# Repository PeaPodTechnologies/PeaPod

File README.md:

# PeaPod <!-- omit in toc -->

A cloud-connected isolated and automated plant growth environment, able to generate any environment from a combination of independent environment parameters. 

Designed as both a hassle-free food production system and a research tool for precise and distributed mapping of the plant-environment relationship.

<!-- TODO: Build statuses? etc. -->

Submitted to the [NASA/CSA Deep Space Food Challenge](https://impact.canada.ca/en/challenges/deep-space-food-challenge). _Update_: PeaPod has [won](https://impact.canada.ca/en/challenges/deep-space-food-challenge/semi-finalists) Phase 1 and moved on to prototyping for Phase 2!

***

### Table of Contents

- [Background](#background)
  - [Features](#features)
- [Production](#production)
- [Development](#development)
- [Contribution](#contribution)
  - [New Issue](#new-issue)
  - [Existing Issues](#existing-issues)
- [Acknowledgements](#acknowledgements)

<!-- include some visuals, i.e. a 3D GIF of the CAD, maybe a flowchart/diagram -->

***

## Background

See our [requirements document](https://github.com/PeaPodTechnologies/PeaPod/blob/staging/docs/requirements/Requirements.pdf).

### Features

See our [progress report](https://github.com/PeaPodTechnologies/PeaPod/blob/staging/docs/RrogressReport.pdf).

<!-- ### Innovations
PeaPod is *not* a fancy container with a light stand. 

PeaPod can **precisely** replicate climates for optimal growing conditions, and also has the ability to collect plant growth data during the growing cycle. 
This data is then used to further *optimize climate parameters* so food grown in PeaPods will taste better over time.

PeaPod is *modular* and *easy to assemble*. 
Construction with aluminum extrusion allows PeaPods to be transported like IKEA furniture, useful for situations where a lot of food is required at the end of a long journey. 
A lot of PeaPods can be collapsed into a tiny space. 
This also means PeaPods can be configured to be any size to grow any type of plant.

PeaPod is self-optimizing, versatile, easy to assemble, and it makes food. -->

***

## Production

<!-- ### Assembly

### Installation

w/ examples, i.e. GIF of expected output, inline code -->

TBA.

***

## Development
<!-- dependencies, environment, languages -->

> See [`software/README`](software/README.md#Development) and the individual [`subsystems`](/subsystems/README.md) for development details.

<br>

## Contribution

### New Issue

1. Open an issue with the features you'd like to add/bugs you'd like to see squashed (admins will add labels, assignments, etc.)
2. Discuss the scope and specifics in the issue, and either:
   1. Make a new branch, make changes, open a **PR Draft** (if you have permissions); or
   2. Fork this repo, make changes, open a **PR Draft**.
3. Request review by changing the **PR Draft** to a full-blown **PR** when you think it's ready.
4. If the reviewer(s) accept the changes, they will merge the **PR** and close the related issue.

### Existing Issues

Check out our [open issues](https://github.com/PeaPodTechnologies/PeaPod/issues?q=is%3Aopen+is%3Aissue+label%3A%22Status%3A+Open%22)!

<!-- ### Support -->
<!-- issues page, discussion board/Discord? -->

<br>

## Acknowledgements

Sincere thanks to the following individuals and groups:
- MIT Media Lab's Open Agriculture Initiative (for inspiration)
- The Open Source community
- Deep Space Food Challenge administrators and participants

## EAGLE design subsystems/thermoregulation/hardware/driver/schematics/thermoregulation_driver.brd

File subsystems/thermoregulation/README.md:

# PeaPod Thermoregulation Subsystem

## Purchasing

TODO: Notes on PCB ordering, multiple BoMs, etc.

## Assembly

## Testing

### Method

### Results

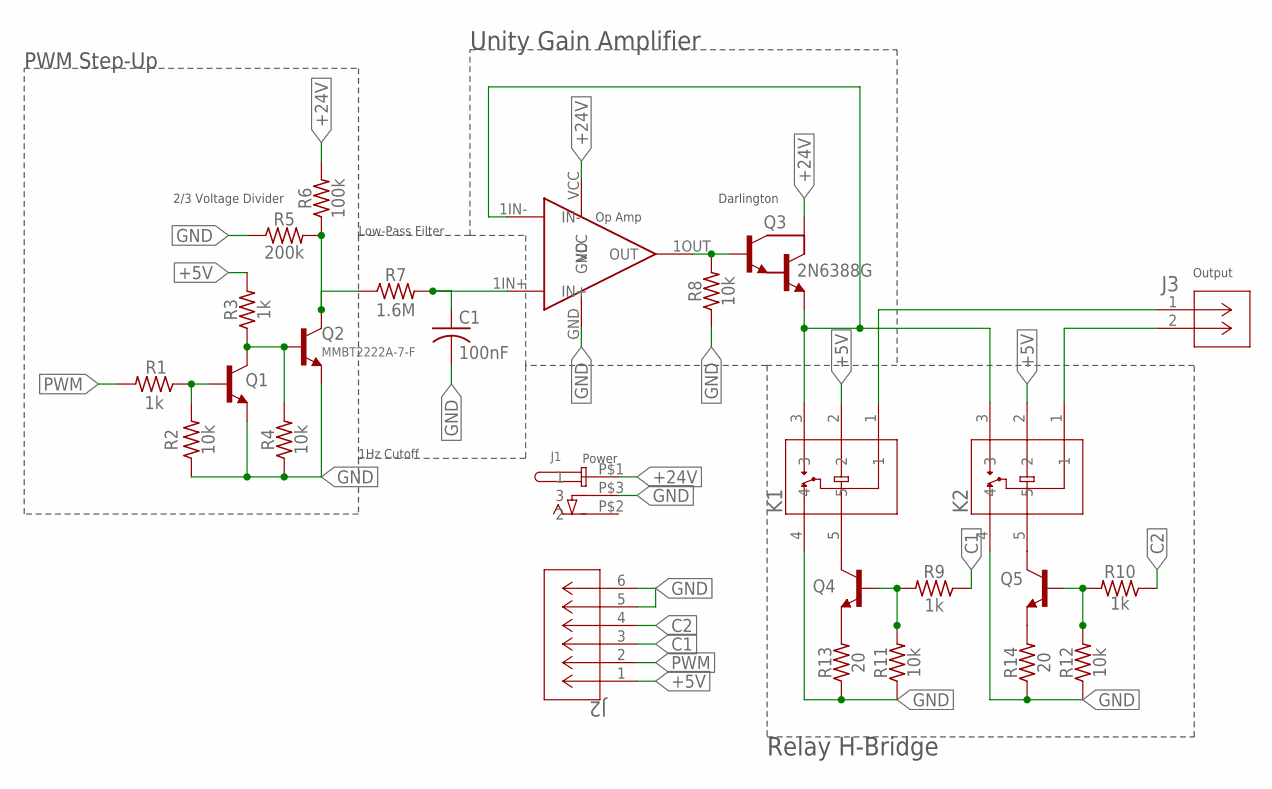
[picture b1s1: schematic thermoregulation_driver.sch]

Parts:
C1: 100nF; CAPC1005X60
J1: DCBARRELJACK
J2: MOLEX-MICROLOCK-6PIN; CON_5055670671
J3: 436500201CON_436500201_MOL; CON_436500201_MOL
K1, K2: G5LE-14_DC12RELAY_G5LE-1_DC5_OMR; RELAY_G5LE-1_DC5_OMR
OPAMP1: LM324N
Q1, Q4, Q5: NPN; SOT95P237X112-3N
Q2: MMBT2222A-7-F; SOT95P237X112-3N
Q3: 2N6388G; TO220
R1, R3, R9, R10: 1k; RESC1005X40
R2, R4, R8, R11, R12: 10k; RESC1005X40
R5: 200k; RESC1005X40
R6: 100k; RESC1005X40
R7: 1.6M; RESC1005X40
R13, R14: 20; RESC2012X65

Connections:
+5V: J2.1, K1.2, K2.2, R3.2
+24V: J1.P$1 (1), OPAMP1.VCC, Q3.C, R6.2
C1: J2.3, R9.1
C2: J2.4, R10.1
GND: C1.2, J1.P$3 (3), J2.5, J2.6, K1.4, K2.4, OPAMP1.GND, Q1.2 (E), Q2.2 (E), R2.1, R4.1, R5.1, R8.1, R11.1, R12.1, R13.1, R14.1
unnamed: Q2.3 (C), R5.2, R6.1, R7.1
unnamed: Q1.3 (C), Q2.1 (B), R3.1, R4.2
unnamed: C1.1, OPAMP1.1IN+ (IN+), R7.2
unnamed: OPAMP1.1OUT (OUT), Q3.B, R8.2
unnamed: Q1.1 (B), R1.1, R2.2
unnamed: K1.3, K2.3, OPAMP1.1IN- (IN-), Q3.E
unnamed: J3.1, K1.1
unnamed: J3.2, K2.1
unnamed: K1.5, Q4.3 (C)
unnamed: K2.5, Q5.3 (C)
unnamed: Q4.1 (B), R9.2, R11.2
unnamed: Q5.1 (B), R10.2, R12.2
unnamed: Q4.2 (E), R13.2
unnamed: Q5.2 (E), R14.2
PWM: J2.2, R1.2

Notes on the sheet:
PWM Step-Up
Low-Pass Filter
1Hz Cutoff
2/3 Voltage Divider
Unity Gain Amplifier
Darlington
Op Amp
Relay H-Bridge
Output
Power

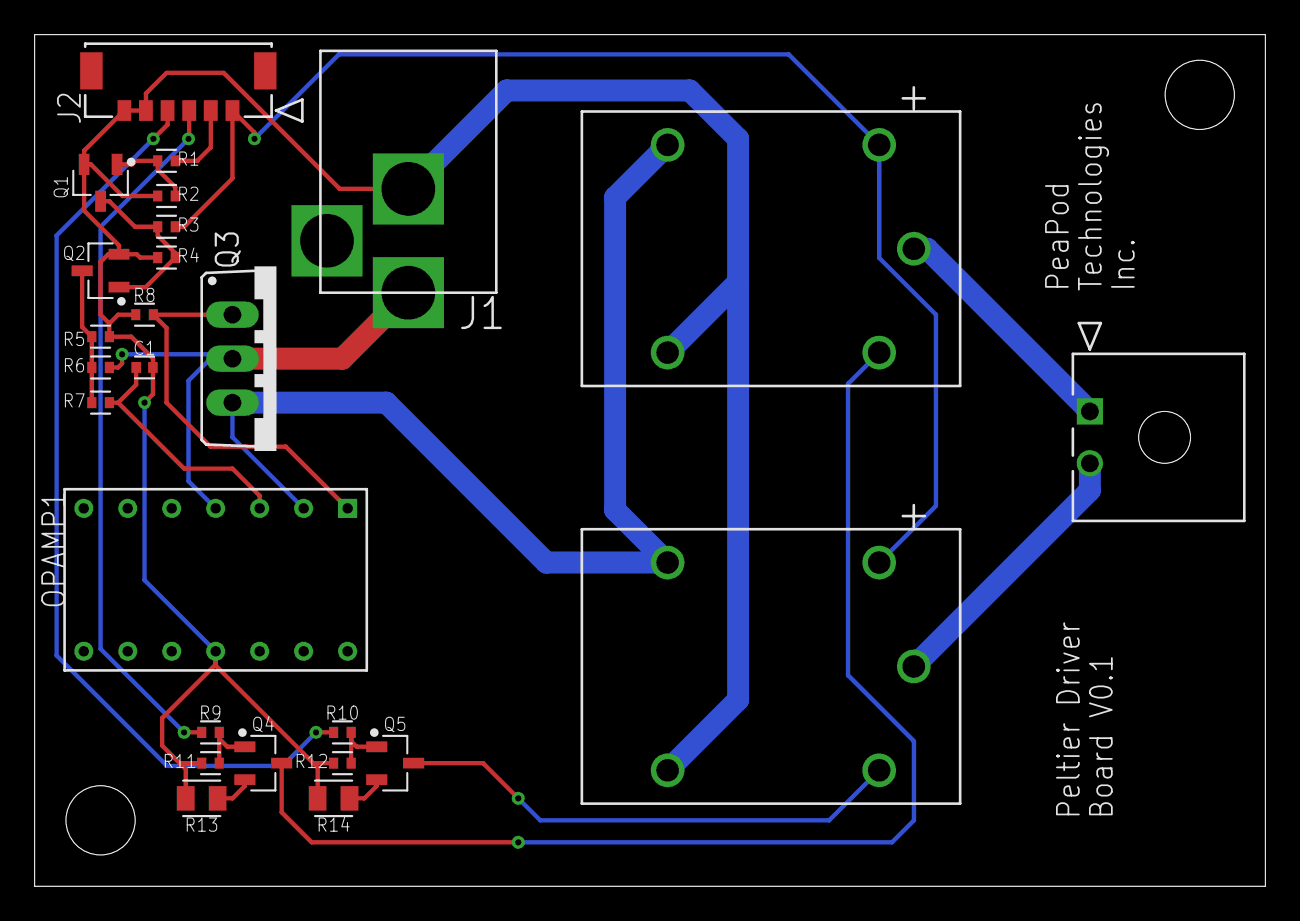
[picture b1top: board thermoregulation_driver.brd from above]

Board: 2 copper layers, 71.1 x 49.2 mm, 26 parts (0 on the bottom side), 20 nets.

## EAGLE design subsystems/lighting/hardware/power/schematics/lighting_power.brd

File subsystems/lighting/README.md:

# PeaPod Lighting Subsystem

See `./REQUIREMENTS.md` for the subsystem requirements.

Provides controlled light to the plant canopy and supports programmable photoperiods (on/off), light intensity (dimming), and spectral channel control via Adafruit PCA9685 PWM dimming of MEAN WELL LDD-L constant-current LED drivers powering CREE XLAMP LEDs with a variety of spectra, including PAR and white for imaging. Power regulator, I2C cables, and PCBs are documented swappable components.

# Production

## Assembly

### Bills of Materials

<!-- TODO: Cables?? -->

See `./hardware/lighting_bom_purchase.csv` for the purchase bill of materials. See `./hardware/gerber/` for PCB manufacturing files (NOTE: STENCIL NECESSARY). See `./hardware/lighting_bom_components.csv` for the electronic components bill of materials (DigiKey).

1. 1 x Lighting BOM Components per led board
2. 1 x Lighting BOM Purchase per led board

### Tools and Equipment

Required:
- Soldering Iron, Solder, and Flux
- Wire Strippers (20-30 AWG)
- Reflow Oven (or hot air rework station) and solder paste
- Putty Scraper

Optional, but recommended:
- Helping Hands (for soldering)
- Multimeter (for testing connections)
- Oscilloscope (for testing signal integrity)
- Luminous Flux Meter (for measuring light output)

## Instructions

1. Using a putty scraper, apply solder paste to the PCB using the stencil.
2. Place the surface-mount components (signal connector, resistor, and LEDs) on the PCB according to the silkscreen.
3. Reflow the PCB in a reflow oven (or use a hot air rework station) to solder the surface-mount components.
4. Solder the through-hole components (power connector and LED driver) to the PCB according to the silkscreen.

## Testing

### Power Test

**Protocol**: Connect the 24V power supply (+24VDC and GND) to the power connector on the PCB.

**Validation**: Nothing happens. Test points TP3 and TP4 read +24V and 0V, respectively.

**Failure Protocol**: 

1. *Smoke, Sparks or Unusual Heat/Odors*: Immediately disconnect the power supply. Check the PCB for solder bridges or shorts. If issue persists, check the power supply and ensure it is functioning correctly.

2. *Incorrect Voltage Readings*: Check the power supply connections and ensure the PCB is properly soldered.

### LED Light Test

**Protocol**: Connect the 24V power supply (+24VDC and GND) to the power connector on the PCB. Flash an Arduino-compatible microcontroller with the `./software/tests/Test_SingleWave/Test_SingleWave.ino` sketch. Connect the microcontroller to the signal connector on the PCB (Digital Pin 3 and GND). Observe the behavior of the LEDs.

**Validation**: The LEDs should light up in a sinusoidal wave pattern, with the brightness varying smoothly over time.

**Failure Protocol**: Check the power supply connections and ensure the PCB is properly soldered. Check test points TP3 and TP4 for correct voltage levels. Check the microcontroller connections to the signal connector and ensure the correct pin is used. Check test point TP5 for PWM signal using an oscilloscope. If issue persists, check the microcontroller code and ensure it is functioning correctly.

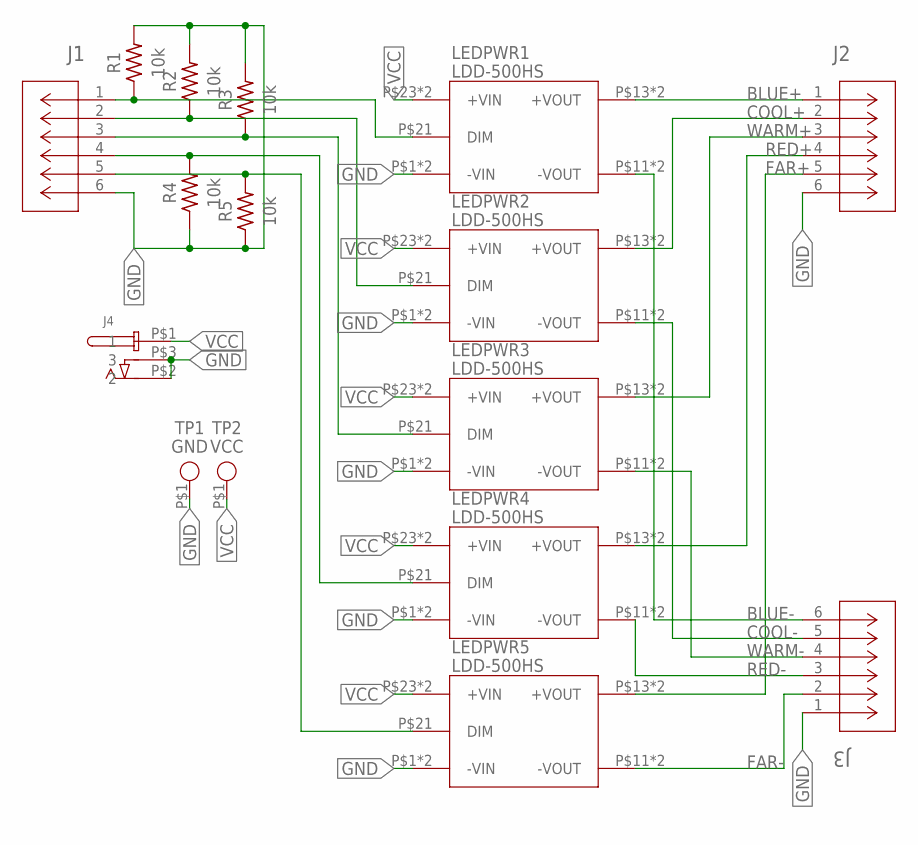
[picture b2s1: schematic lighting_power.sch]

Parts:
J1, J2, J3: MOLEX-MICROLOCK-6PIN; CON_5055670671
J4: DCBARRELJACK
LEDPWR1, LEDPWR2, LEDPWR3, LEDPWR4, LEDPWR5: LDD-500HS; LDD-300~1000HS
R1, R2, R3, R4, R5: 10k; RESC1005X40
TP1: GND; TP_CIRCLE_2.5MM
TP2: VCC; TP_CIRCLE_2.5MM

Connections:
BLUE+: J2.1, LEDPWR1.P$13 (+VOUT), LEDPWR1.P$14 (+VOUT)
BLUE-: J3.6, LEDPWR1.P$11 (-VOUT), LEDPWR1.P$12 (-VOUT)
COOL+: J2.2, LEDPWR2.P$13 (+VOUT), LEDPWR2.P$14 (+VOUT)
COOL-: J3.5, LEDPWR2.P$11 (-VOUT), LEDPWR2.P$12 (-VOUT)
FAR+: J2.5, LEDPWR5.P$13 (+VOUT), LEDPWR5.P$14 (+VOUT)
FAR-: J3.2, LEDPWR5.P$11 (-VOUT), LEDPWR5.P$12 (-VOUT)
GND: J1.6, J2.6, J3.1, J4.P$3 (3), LEDPWR1.P$1 (-VIN), LEDPWR1.P$2 (-VIN), LEDPWR2.P$1 (-VIN), LEDPWR2.P$2 (-VIN), LEDPWR3.P$1 (-VIN), LEDPWR3.P$2 (-VIN), LEDPWR4.P$1 (-VIN), LEDPWR4.P$2 (-VIN), LEDPWR5.P$1 (-VIN), LEDPWR5.P$2 (-VIN), R1.2, R2.2, R3.2, R4.1, R5.1, TP1.P$1
unnamed: J1.1, LEDPWR1.P$21 (DIM), R1.1
unnamed: J1.2, LEDPWR2.P$21 (DIM), R2.1
unnamed: J1.3, LEDPWR3.P$21 (DIM), R3.1
unnamed: J1.4, LEDPWR4.P$21 (DIM), R4.2
unnamed: J1.5, LEDPWR5.P$21 (DIM), R5.2
RED+: J2.4, LEDPWR4.P$13 (+VOUT), LEDPWR4.P$14 (+VOUT)
RED-: J3.3, LEDPWR4.P$11 (-VOUT), LEDPWR4.P$12 (-VOUT)
VCC: J4.P$1 (1), LEDPWR1.P$23 (+VIN), LEDPWR1.P$24 (+VIN), LEDPWR2.P$23 (+VIN), LEDPWR2.P$24 (+VIN), LEDPWR3.P$23 (+VIN), LEDPWR3.P$24 (+VIN), LEDPWR4.P$23 (+VIN), LEDPWR4.P$24 (+VIN), LEDPWR5.P$23 (+VIN), LEDPWR5.P$24 (+VIN), TP2.P$1
WARM+: J2.3, LEDPWR3.P$13 (+VOUT), LEDPWR3.P$14 (+VOUT)
WARM-: J3.4, LEDPWR3.P$11 (-VOUT), LEDPWR3.P$12 (-VOUT)

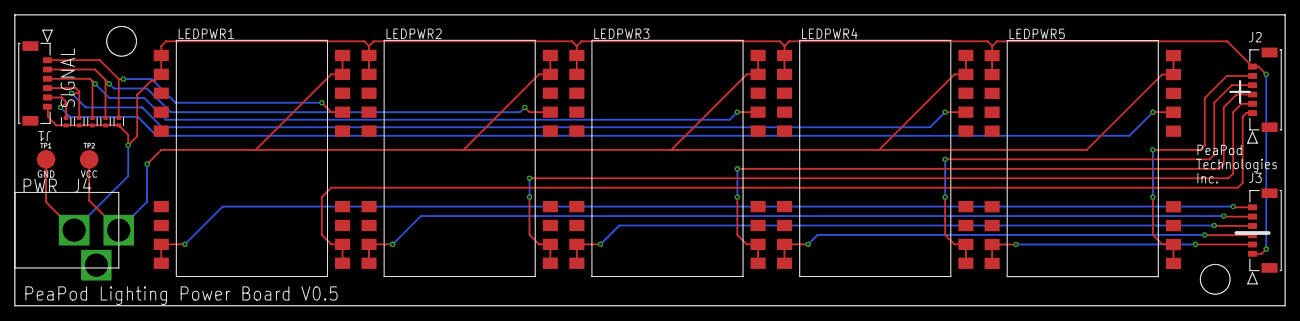
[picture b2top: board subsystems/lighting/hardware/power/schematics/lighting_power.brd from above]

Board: 2 copper layers, 170.8 x 39.1 mm, 16 parts (0 on the bottom side), 17 nets.

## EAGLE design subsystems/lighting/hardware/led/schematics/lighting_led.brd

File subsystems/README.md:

# PeaPod Subsystems

All subsystems will follow the same structure:

- `README.md` - Detailed instructions for fabrication and purchasing, list of materials incl. tools, assembly instructions with graphics, testing and validation protocol, method of operation, and expected results.
- `REQUIREMENTS.md`
- `assets/` - various graphical/etc. assets (diagrams, etc. excluding pictures of schematics/PCB layouts)
- `hardware/`
- `software/`

In addition, each subsystem should have its own `README.MD` with the following info:

- Purchasing
- Assembly w/ photos
- Testing (process and results)

## Hardware

Includes all **reference** bills of materials (BOM), 3D printing files, PCB files, etc.

Subdirectories:

- `boms/` - Bills of Materials (CSV files)
- `fabrication/` - Fabricated part files (i.e. 3D printing files)
- `schematics/` - PCB schematics (.SCH and .BRD files and photos of each)
- `gerber/` - Gerber files (PCB manufacturing)

## Software

Includes all C/C++ libraries and Arduino testing scripts.

Subdirectories:

- `src/` - Libraries
- `tests/` - Test scripts

# Development

Component BOMs downloaded from [DigiKey](https://www.digikey.ca) (can be directly uploaded for ordering). All other BoM types (fabrication, purchase, etc.) copied from the [BoM Templates](/.github/BOM_TEMPLATES/). 3D models, PCB and schematic docs are made using [AutoDesk Fusion 360](https://www.autodesk.ca/en/products/fusion-360/overview).

## Requirements

- Fusion 360 or your 3D editor of choice
- EasyEDA or your PCB/schematic editor(s) of choice
- Excel/Google Sheets or your CSV reader/spreadsheet software of choice

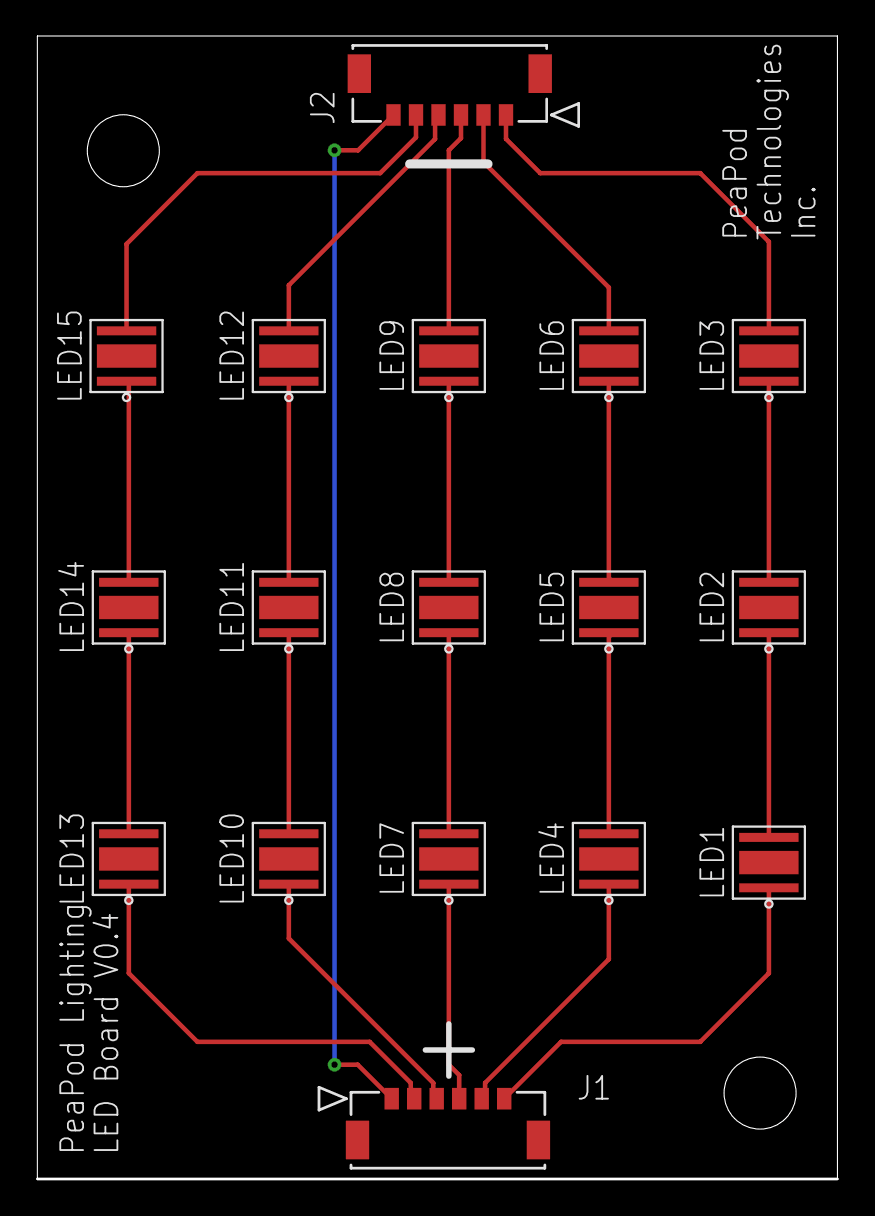
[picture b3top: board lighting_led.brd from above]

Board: 2 copper layers, 44.5 x 63.4 mm, 17 parts (0 on the bottom side), 21 nets.

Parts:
J1, J2: MOLEX-MICROLOCK-6PIN; CON_5055670671
LED1, LED2, LED3: XP-G3_BLUE; XLAMP_XP-G3_BLUE
LED4, LED5, LED6: XP-G3_COOL; XLAMP_XP-G3_COOL
LED7, LED8, LED9: XP-G3_WARM; XLAMP_XP-G3_WARM
LED10, LED11, LED12: XP-G3_RED; XLAMP_XP-G3_RED
LED13, LED14, LED15: XLAMP_XP-E2

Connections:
unnamed: LED4.P$2, LED5.P$1
unnamed: LED1.P$2, LED2.P$1
unnamed: LED2.P$2, LED3.P$1
unnamed: LED5.P$2, LED6.P$1
unnamed: LED7.P$2, LED8.P$1
unnamed: LED8.P$2, LED9.P$1
unnamed: LED10.P$2, LED11.P$1
unnamed: LED11.P$2, LED12.P$1
unnamed: LED13.P$2, LED14.P$1
unnamed: LED14.P$2, LED15.P$1
unnamed: J1.6, LED1.P$1
unnamed: J1.5, LED4.P$1
unnamed: J1.4, LED7.P$1
unnamed: J1.3, LED10.P$1
unnamed: J1.2, LED13.P$1
unnamed: J1.1, J2.6
unnamed: J2.5, LED15.P$2
unnamed: J2.4, LED12.P$2
unnamed: J2.3, LED9.P$2
unnamed: J2.2, LED6.P$2
unnamed: J2.1, LED3.P$2

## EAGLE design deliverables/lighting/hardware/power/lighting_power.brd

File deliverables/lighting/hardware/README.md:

# Lighting Hardware

TODO: Notes on PCB ordering, multiple BoMs, etc.

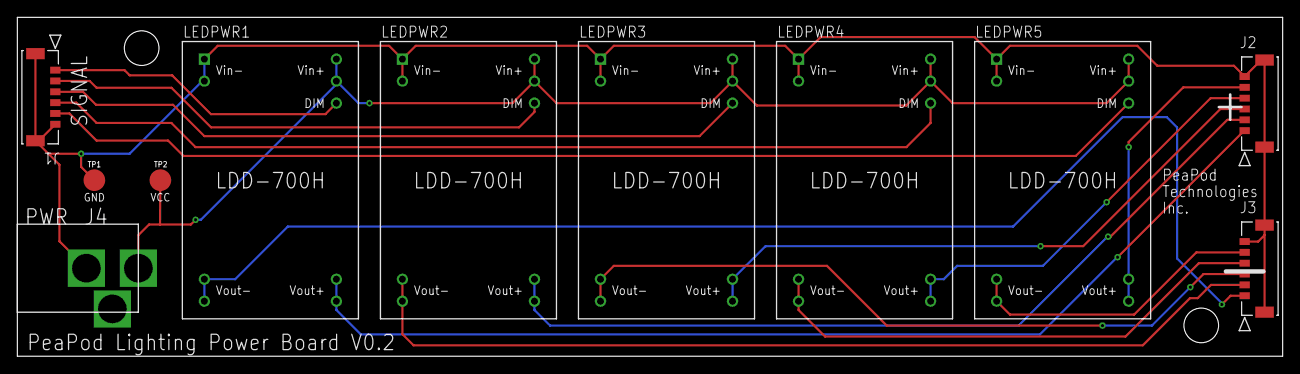
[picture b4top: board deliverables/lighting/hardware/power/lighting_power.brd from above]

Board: 2 copper layers, 146.1 x 39.1 mm, 11 parts (0 on the bottom side), 17 nets.

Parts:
J1, J2, J3: MOLEX-MICROLOCK-6PIN; CON_5055670671
J4: DCBARRELJACK
LEDPWR1, LEDPWR2, LEDPWR3, LEDPWR4, LEDPWR5: LDD-700H; NLDD-300~1000H
TP1: GND; TP_CIRCLE_2.5MM
TP2: VCC; TP_CIRCLE_2.5MM

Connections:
GND: J1.6, J1.7, J1.8, J2.6, J2.7, J2.8, J3.6, J3.7, J3.8, J4.P$3, LEDPWR1.VIN-1, LEDPWR1.VIN-2, LEDPWR2.VIN-1, LEDPWR2.VIN-2, LEDPWR3.VIN-1, LEDPWR3.VIN-2, LEDPWR4.VIN-1, LEDPWR4.VIN-2, LEDPWR5.VIN-1, LEDPWR5.VIN-2, TP1.P$1
unnamed: J1.1, LEDPWR1.DIM
unnamed: J1.2, LEDPWR2.DIM
unnamed: J1.3, LEDPWR3.DIM
unnamed: J1.4, LEDPWR4.DIM
unnamed: J1.5, LEDPWR5.DIM
unnamed: J2.1, LEDPWR1.VO+1, LEDPWR1.VO+2
unnamed: J2.2, LEDPWR2.VO+1, LEDPWR2.VO+2
unnamed: J2.3, LEDPWR3.VO+1, LEDPWR3.VO+2
unnamed: J2.4, LEDPWR4.VO+1, LEDPWR4.VO+2
unnamed: J2.5, LEDPWR5.VO+1, LEDPWR5.VO+2
unnamed: J3.1, LEDPWR1.VO-1, LEDPWR1.VO-2
unnamed: J3.2, LEDPWR2.VO-1, LEDPWR2.VO-2
unnamed: J3.3, LEDPWR3.VO-1, LEDPWR3.VO-2
unnamed: J3.4, LEDPWR4.VO-1, LEDPWR4.VO-2
unnamed: J3.5, LEDPWR5.VO-1, LEDPWR5.VO-2
VCC: J4.P$1, LEDPWR1.VIN+1, LEDPWR1.VIN+2, LEDPWR2.VIN+1, LEDPWR2.VIN+2, LEDPWR3.VIN+1, LEDPWR3.VIN+2, LEDPWR4.VIN+1, LEDPWR4.VIN+2, LEDPWR5.VIN+1, LEDPWR5.VIN+2, TP2.P$1

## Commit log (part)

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2021-07-16 added storyboard frame revisions
2021-07-17 Removed Review Frames
2021-07-17 Added Setup Frames, Pollination
2021-07-18 Wrote Blockchain
2021-07-18 Revision, Formatting
2021-07-19 New Method Structure to Template
2021-07-19 Housing Method Revision
    formatted features
2021-07-19 Contact Info Formatting
2021-07-20 Nutrients, pH Method Revision
2021-07-20 Script Condensing, Modifying
2021-07-20 Injection Manifold Method Revision
2021-07-20 Added to safety of produce section
2021-07-20 Air Temperature Method Revision
    changed spacing
2021-07-20 Dehumidification Method Revision
2021-07-20 Solution Temperature Method Revision
2021-07-20 Optimization, Formatting, Justification Integration
2021-07-21 Updated Version
2021-07-21 revised
2021-07-21 revised
    @JonasMarshall
2021-07-22 Fixed PR#87
2021-07-22 Acceptability of Process pt. 1
2021-07-23 Fix Table of Contents
2021-07-24 Voiceover
2021-07-24 Setup Process Timing Estimates
2021-07-26 mentioned a recycling pump
2021-07-26 Acceptability of Products
2021-07-27 Added "Runoff"
2021-07-27 Better Terrestrial Prompts
2021-07-27 Script to Description Part A
    added basc to jonas's description
2021-07-27 Whole-Design Breakdown
    commented out figures
    rotated design process 90deg
2021-07-28 Update Customer-facing Food Service
2021-07-28 Update Crowdsourced Research
2021-07-28 Un-OOPS
2021-07-28 Description A: Optimization
2021-07-28 Update De-centralized Production
2021-07-28 Added first 1000 characters of innovation section
2021-07-28 Update Innovation
2021-07-28 Minor Fix
2021-07-29 Revisions
2021-07-29 Minor Fix 2: Electric Boogaloo
2021-07-29 Description Revision
2021-07-29 Copyright Ownership Transferred
2021-07-29 Final Script
    removed old voiceover
2021-07-30 1st Cut to Design Abstract
2021-07-30 3rd Cut to Design Abstract
    Sub char limit
2021-07-30 Citations Part A
2021-07-30 1st Cut to Part A
    Also final cut to Abstract
2021-07-30 2nd Cut to Part A
    2029 Characters Over
2021-07-30 Cut Description B
2021-07-30 Cut Constraints
    moved estimates to appendix
    fixed citations
2021-07-30 2nd Cut to Innovation
    487 characters over
2021-07-30 Final Cut to Innovation
    42 characters under
2021-07-30 Final Cut to Terrestrial
    13 characters under
2021-07-30 Cut Down Performance Criteria
2021-07-30 Formatting
2021-07-30 Namedropped Pollination
2021-07-30 Minor Additions
2021-07-31 Link to Animation in Readme
2021-08-01 Easier Open-Source Contribution
2021-08-05 Solution Overview: Insulation
2021-08-06 Finished Calculations
2021-08-17 Updated for Door
2021-09-13 Squashed commit of the following:
    commit edd2e320934a10050e6a734e7f221cd0c52407a9
    Author: Jayden Lefebvre <jayden.lefebvre55@gmail.com>
    Date: Mon Sep 13 15:41:54 2021 -0400
    Delete actuator class
    commit 215b883cccbcfc56583e870d5dec005db6cc2654
    Merge: 85135fe 7164cfe
2021-09-27 Siphon Injector, BoM updates
2021-09-28 Refactored to UpRoute
2021-10-13 Removed DSFC, Assembly Docs
2021-10-13 Added Validation, Verification to Design Issue Template
2021-10-13 BoM Updates
    Finished https://github.com/UpRouteFoundation/PeaPod/issues/50#issuecomment-877507976
    Made sure older listings matched CAD and prototype
    Left the ones that were going to be outdated eventually
2021-10-13 Dehumidification
2021-10-24 The FINAL Doc/License Refactor
2021-10-25 Lighting Boards V0.2
2021-10-25 Minor Changes
    Used built-in constrain function
    Removed LED brightness factor coefficient (allows full power addressing)
2021-10-26 Added Supporting Files for V0.2
    SCH, BRD, and PNG for both
    Also FBX models
2021-10-27 Added Aeroponics Input Connectors
2021-10-28 Structure Overhaul
2021-10-28 Fix Broken Links
2021-11-06 Cleanup
2021-11-10 Software Restructure
2021-11-10 Batch Publishing
    Also: batch data logging, better startup scripts, restructured main
2021-11-10 Publish Logging - Use Reduce
2021-11-10 Project/Run Select, Offline Publishing
2021-11-12 Multiple Small Changes
    Added Info Spinner
    Changed main from async to return Promise, better error handling
2021-11-14 Change Contact Emails
2021-11-16 Removed Panel Mounts
2021-11-16 Updated BoM References
    Also removed seal strip stl
2021-11-20 Microcontroller Communications
    Start Publisher before Arduino (reversed promise nesting order)
    Fixed serial parser piping
    Better console logging
    Fixed Arduino JSON handling (manual \n instead of println, full revision message)
2021-11-20 Moved Arduino Code to /software
    also renamed to PeaPodOS-Arduino
2021-11-20 Minor Updates
2021-11-26 Lighting V0.4
    FINALLY fixed the connector flipping error (hint: pin 1 goes to pin 6 EVERY TIME)
    Flipped LED series order (blue on bottom)
    More "bus"-like routing on power PCB
    Updated version number text on PCBs
2021-11-26 Standardized Trace Width
    10mil on all traces (~8C rise at .7A)
2021-12-31 Small Changes
2022-01-07 Added Phase 2 Instructions to References
2022-01-09 Modularized Reference Designs
2022-01-09 Added UTAG To Namecard
2022-01-09 Requirements Graph
2022-01-09 Outlined Progress Report
2022-01-11 Outlined Final Report, Cleanup
    modularizing reused sections
    docs/ readme
2022-01-16 Fixes
2022-01-27 Improved Calculations
    added thermal resistance calculations
    added peltier driver circuit
2022-01-27 Bump follow-redirects from 1.14.5 to 1.14.7 in /software
    Bumps [follow-redirects](https://github.com/follow-redirects/follow-redirects) from 1.14.5 to 1.14.7.
    - [Release notes](https://github.com/follow-redirects/follow-redirects/releases)
    - [Commits](https://github.com/follow-redirects/follow-redirects/compare/v1.14.5...v1.14.7)
    ---
    updated-dependencies:
    - dependency-name: follow-redirects
2022-01-27 LED Class Improvements
    led color enum, parsing to String
2022-02-03 Setup
2022-02-04 Peltier Driver V0.1
2022-02-11 early draft testing plan + control points
    basically a frame, need to ask questions then can fill it out properly
2022-02-21 Testing Suite, ICSP Flashing
    Tests: GPIO miniUART serial port functionality (loopback test), compilation and upload test (blink), revision check test
    Arduino compile and flash utility function (utils)
    Readme overhaul
    Removed deprecated Arduino libraries (scale, nau7802, float)
2022-03-02 Moved Report TeX Class
2022-03-02 Modularized Solution Overview
2022-03-04 Minor Changes
    Arduino accepts empty instruction set
    Fixed spinner log ui util
    Better C++ styling (header order, file naming, #include protection naming)
2022-03-04 Package v0.0.9
2022-03-16 Migrated to PlatformIO
    * Migrated to PlatformIO for compilation
    * Separated JSON messaging, instruction parsing into utility files
    * Moved globals to header
    + PIO Testing Suite
    * Updated README
2022-03-18 TypeScript Unit Testing
    * Fixed PIO unit testing
    * JSON messenger returns instead of printing to serial during unit tests
    * main.cc ignored during unit tests
    * Moved lib/ to src/
    + Setup jest
    + Utils unit tests
2022-03-19 Fixed Unit Tests
    * Fixed TS compiling for RPi Node version (12.22.x)
    * No longer running test_instructions or test_messenger (awaiting fix)
2022-03-25 Actuator Control
    + Direct Arduino instruction set command via GCP
    * Fixed actuator target statefulness
    - no more ignored tests
    - no more "F" PSTR
    * Fixed TS serial write error handling
2022-04-06 Aeroponic Container
    * Updated plumbing diagram, BoM
    - Removed old "assembled" photo
    * New tray mounts
    * Renamed other housing fabrication files
    - Removed siphon injectors
2022-05-03 GPIO Utils, Arduino Reset on Start
    + Utils for exporting, unexporting, writing to, and reading from GPIO pins via sysfs
    + Testing suite for new utils
    * Arduino reset pin pulled high on start
2022-05-03 Restructured Data Batches
    * De-nested, from {"air-temperature":{batch:[...]},...} to {"air-temperature":[...],...}
2022-05-11 Overhaul
    * Simulated interfaces accessible only via unit testing
    + Util methods for compound .env checking, returning and loading to objects
    * Moved "simulated" interfaces to be in the same file as the classes they simulate
    + PeaPod class
    + More+better variable description comments
    * Refactored "arduino" to "controller"
2022-05-25 Restructuring
    - Removed solution overview (too similar to progress report, will likely refactor back after dsfc)
    * Moved, combined subsystem doc fragments
2022-05-26 Added notes
2022-05-27 Restructured Doc, Added Graphics
    + Solenoid lock
2022-05-28 Process Description
    * Improved equations
    + Added parts
    * improved layout, page breaks
2022-05-28 Restructuring
2022-05-29 System Description
    removed animation folder
    moved design report out of archive
2022-05-30 Materials: Automation
2022-05-30 Aeroponic Container
2022-05-30 Update Sample Collection for Safety of Outputs
2022-05-30 Materials: Housing
2022-05-30 Materials: Thermoregulation
2022-05-30 Materials: Thermoregulation pt. 2
2022-05-30 Update TestingPlan.tex
    Small addition to safety
2022-05-30 Added Desiccant, Air Filters
2022-05-30 Materials: Maintenance and Cleaning
2022-05-31 Update Testing Plan - By-Product Safety
2022-05-31 Update Testing Plan - incorporate feedback
2022-06-01 Prototype Progress
2022-06-01 Convert to Markdown
2022-06-01 Hazard Analysis: Seeds
2022-06-01 Hazard Analysis: Testing
2022-06-02 Bump protobufjs from 6.11.2 to 6.11.3 in /software
    Bumps [protobufjs](https://github.com/protobufjs/protobuf.js) from 6.11.2 to 6.11.3.
    - [Release notes](https://github.com/protobufjs/protobuf.js/releases)
    - [Changelog](https://github.com/protobufjs/protobuf.js/blob/v6.11.3/CHANGELOG.md)
    - [Commits](https://github.com/protobufjs/protobuf.js/compare/v6.11.2...v6.11.3)
    ---
    updated-dependencies:
2022-06-05 Testing Plan & HACCP v1
2022-06-19 Minor Fix
    Made intervals private fields
2022-07-05 Fixed Reset
    - Removed sysfs GPIO util functions
    + Implemeneted `onoff` package GPIO
2022-07-12 Formatting, Refactoring
    Updated OpenAG reference design
2022-07-15 Supply Pump, Solenoid Actuators
2022-07-16 Idle State
2022-07-29 Microcontroller Optimization, UX, Interrupts
    + Added sensor and actuator name strings (progmem), toString methods
    * Moved datasetup to progmem
    * Moved globals to static class properties
    * Replaced all String with c strings
    + Added InterruptHandler interface to allow hardware interrupts to modify object instance data using a small hack
    * Modified variable storage properties where fitting (i.e. const char* const* as opposed to const char**)
2022-07-29 Microcontroller Modular Unit Tests
2022-08-29 added linting and extensions for vscode
2022-11-12 Bump minimatch from 3.0.4 to 3.1.2 in /software
    Bumps [minimatch](https://github.com/isaacs/minimatch) from 3.0.4 to 3.1.2.
    - [Release notes](https://github.com/isaacs/minimatch/releases)
    - [Commits](https://github.com/isaacs/minimatch/compare/v3.0.4...v3.1.2)
    ---
    updated-dependencies:
    - dependency-name: minimatch
2023-01-29 Form Prompts
2023-01-30 algae haccp
2023-01-31 Broke Out Design Report, Integrated Into Final Report
2023-01-31 Updated algae cleaning processes
2023-02-02 Bump jszip from 3.7.1 to 3.10.1 in /software
    Bumps [jszip](https://github.com/Stuk/jszip) from 3.7.1 to 3.10.1.
    - [Release notes](https://github.com/Stuk/jszip/releases)
    - [Changelog](https://github.com/Stuk/jszip/blob/main/CHANGES.md)
    - [Commits](https://github.com/Stuk/jszip/compare/v3.7.1...v3.10.1)
    ---
    updated-dependencies:
2025-08-29 Docs WIP
2025-08-29 Archived WIP
2025-08-29 Import Main Script
2025-08-31 Add I2CIP
2025-09-25 Watering, Lighting Modules w/ Tests
2025-09-27 Added ADC
2025-12-19 Update workspace files and normalize line endings
2026-01-06 Made Frontend Selectable
2026-01-06 SerialPort Scanner
2026-01-11 State Table
2026-01-11 System Report V1
2026-01-12 Cleanup, Readme
2026-01-14 State Editor
2026-01-17 Firmware Flashing
2026-01-22 Fixed FSM Bug
2026-03-02 Docker, Fixed Types
2026-05-04 New Event/Interval Scheduler w/ Calendar, DataGrid
    refactored old scheduler to intervals
2026-05-05 Save & Load Schedules
2026-05-31 Minor Fix Again
2026-05-31 Firebase Camera Upload
2026-05-31 Serial Test
2026-05-31 serialport pt 2
2026-05-31 serialtest pt 4
2026-06-07 serialtest pt5
2026-06-07 Serial Define Order, Docker Builder Output Tar & Install Node Modules
2026-06-10 Better Simulator pt 1
2026-06-11 Requirements Metrics
2026-06-14 Updated Motherboard
2026-06-24 Readmes
2026-06-26 Readmes 3, Menu
2026-06-28 removed requirements graph
2026-06-28 Lighting Overhaul

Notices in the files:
parts and their libraries:
Molex Micro-Lock PLUS 6-pin: COPYRIGHT: Copyright (C) 2018 Accelerated Designs. All rights reserved
COPYRIGHT: Copyright (C) 2022 Ultra Librarian. All rights reserved.
